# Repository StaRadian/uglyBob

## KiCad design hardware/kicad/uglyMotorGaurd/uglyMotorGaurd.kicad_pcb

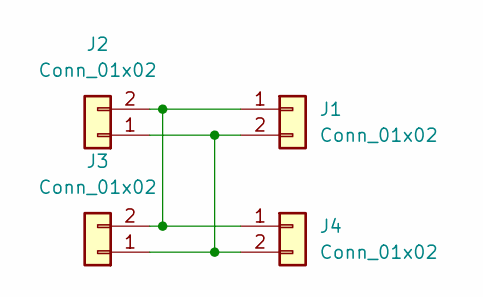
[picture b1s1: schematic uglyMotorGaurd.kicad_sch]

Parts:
J1, J2, J3, J4: Conn_01x02; uglyMotor

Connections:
unnamed: J1.1, J2.2, J3.2, J4.1
unnamed: J1.2, J2.1, J3.1, J4.2

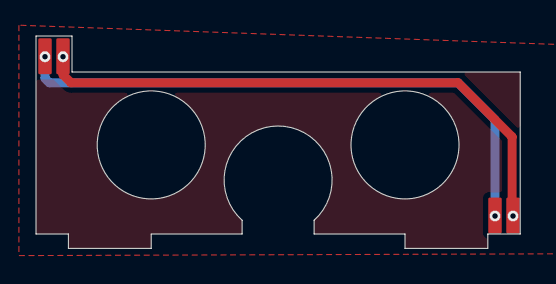
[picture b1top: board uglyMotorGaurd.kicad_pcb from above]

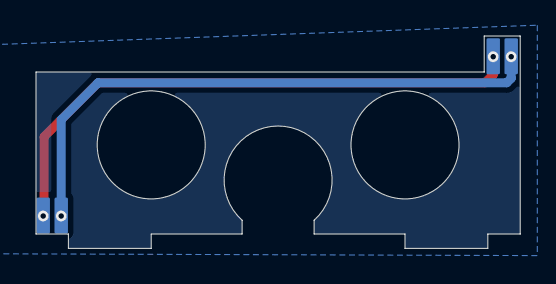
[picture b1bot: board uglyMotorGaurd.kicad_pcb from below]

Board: 2 copper layers, 26.9 x 11.8 mm, 4 parts (2 on the bottom side), 2 nets.

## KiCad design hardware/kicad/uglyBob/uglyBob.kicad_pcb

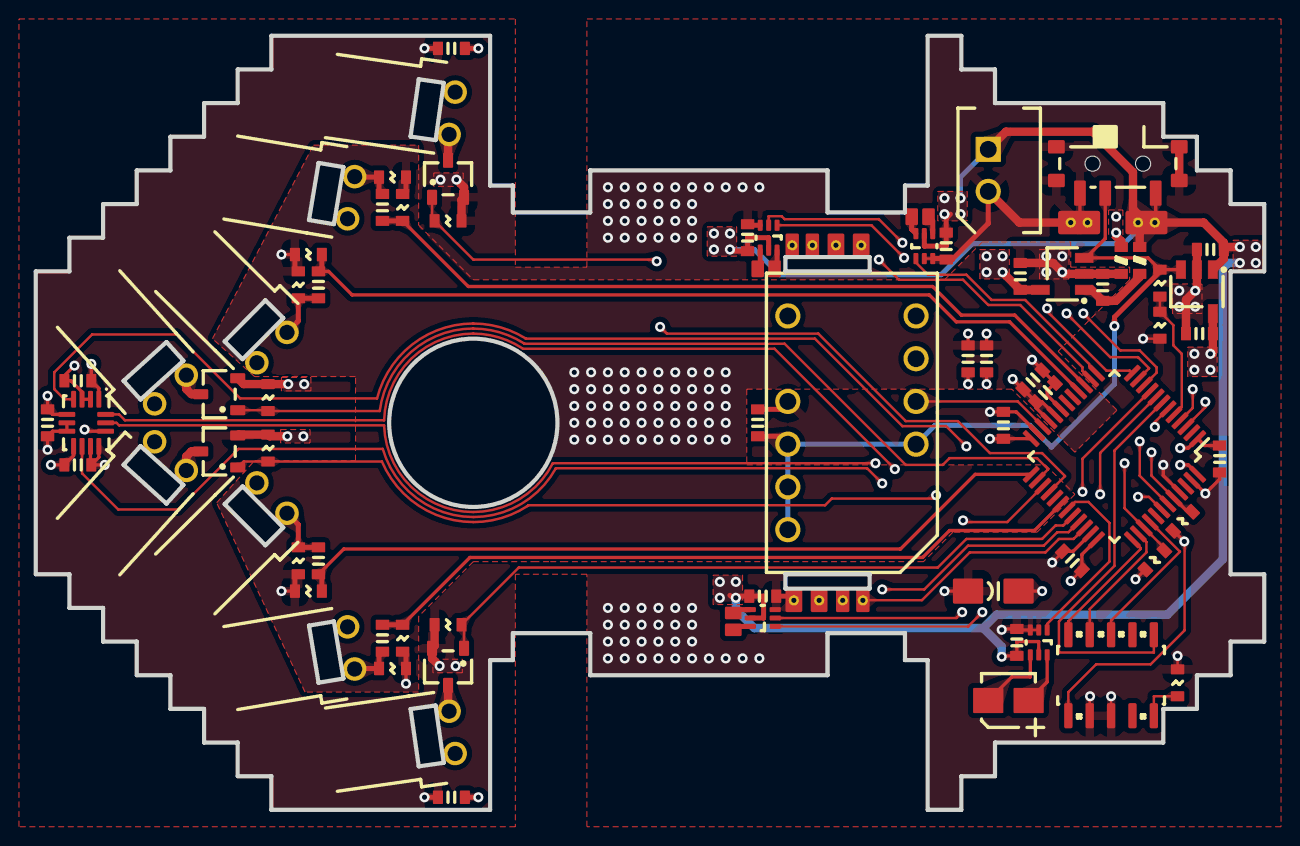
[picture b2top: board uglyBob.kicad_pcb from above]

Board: 4 copper layers, 73.0 x 46.0 mm, 70 parts (0 on the bottom side), 55 nets.

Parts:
BZ1: CMT-322-65-SMT-TR; CMT-332-65-SMT-TR
C1, C2, C3, C4, C5, C6: 1uF; 0603_1608_C
C7, C10, C11, C12, C22, C24, C25, C26, C27, C28: 100nF; 0603_1608_C
C8, C21: 10nF; 0603_1608_C
C9: 4.7uF; 1206_3216_C_Polarized_HandSolder
C13, C14, C15, C16: 2nF; 0603_1608_C
C17, C20, C23: 2.2uF; 0603_1608_C
D1: SFH4550; BobIRLED
FB1, FB2: 600R@100MHz; 0603_1608_L
J1: Battery_Conn; batteryConnector
J2: Charge_Conn; 5267-02A
J3: Conn_02x05_Odd_Even; FTSH-105-01-L-DV-K
J4: Right_Encoder_Conn; AS5047Connector
J5: Left_Encoder_Conn; AS5047Connector
J6: RMotor_Conn; MotorConnector
J7: LMotor_Conn; MotorConnector
J8: SMotor_Conn; MotorConnector
R1: 100; 0603_1608_R
R2, R3, R4, R5, R6, R7, R8, R9: 1.2M; 0603_1608_R
R10, R11, R16, R17: 10k; 0603_1608_R
R12, R13, R14, R15: 30k; 0603_1608_R
SW1: SW_SPDT; EG1215AA
U1, U2: TPS7A2033PDBVR; SOT-23-5_HandSoldering_without4
U3: STM32G4xxC; LQFP-48_7x7mm_P0.5mm
U4: SFH313FA; BobIRSensor
U5, U6, U7, U8: PMV15ENER; SOT-23
U9: ICM-42688-V; LGA-14_2.5x3x0.91_long
U10, U11, U12, U14: DRV8212DRLR; SOT-563
U13: HCMS-390X; HCMS-390x

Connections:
+3.3V: C4.1, C9.1, C10.1, C11.1, C12.1, C17.2, C20.2, C21.2, C22.2, C23.2, D1.FL2 (A), D1.FR2 (A), D1.SL2 (A), D1.SR2 (A), J3.1, J4.3, J5.3, R16.1, R17.1, U2.5 (OUT), U3.1 (VBAT), U3.24 (VDD), U3.36 (VDD), U3.48 (VDD), U9.1 (AP_SDO/AP_AD0), U9.5 (VDDIO), U9.8 (VDD), U9.12 (AP_CS)
+3.3VA: C2.1, C5.1, C6.1, C7.1, C8.1, U1.5 (OUT), U3.20 (VREF+), U3.21 (VDDA), U4.FL1 (C), U4.FR1 (C), U4.SL1 (C), U4.SR1 (C)
+BATT: C3.1, C24.2, C25.2, C26.2, C28.2, FB1.2, J1.1, J2.1, SW1.1 (C), U2.1 (IN), U10.5 (VM), U11.5 (VM), U12.5 (VM), U14.5 (VM)
Batt_voltage: R10.2, R11.1, U3.5 (PF0)
Buzzer_PWM: U3.31 (PA9), U14.1 (IN1)
FL_LED: R12.1, U3.32 (PA10), U5.1 (G1)
FL_SEN: C13.2, R3.1, U3.30 (PA8)
FR_LED: R15.1, U3.28 (PB14), U8.1 (G1)
FR_SEN: C16.2, R9.1, U3.15 (PA7)
GND: C3.2, C4.2, C9.2, C10.2, C11.2, C12.2, C17.1, C20.1, C21.1, C22.1, C23.1, C24.1, C25.1, C26.1, C27.1, C28.1, FB2.1, J1.2, J2.2, J3.3, J3.5, J4.4, J5.4, R1.1, R11.2, R12.2, R13.2, R14.2, R15.2, SW1.3 (A), SW1.EP, U2.2 (GND), U3.23 (VSS), U3.35 (VSS), U3.45 (PB8-BOOT0), U3.47 (VSS), U5.2 (S1), U6.2 (S1), U7.2 (S1), U8.2 (S1), U9.2 (RESV), U9.3 (RESV), U9.6 (GND), U9.7 (RESV), U9.10 (RESV), U9.11 (RESV), U10.3 (GND), U11.3 (GND), U12.2 (IN2), U12.3 (GND), U13.9 (GND), U14.2 (IN2), U14.3 (GND)
GNDA: C1.2, C2.2, C5.2, C6.2, C7.2, C8.2, FB2.2, R2.2, R3.2, R4.2, R5.2, R6.2, R7.2, R8.2, R9.2, U1.2 (GND), U3.19 (VSSA)
HCMS_CE: U3.3 (PC14), U13.7 (CE)
HCMS_CLK: U3.4 (PC15), U13.6 (CLK)
HCMS_DA: U3.22 (PB10), U13.4 (DATA_IN)
HCMS_RS: U3.6 (PF1), U13.5 (RS)
IMU_AP_SCL: R16.2, U3.39 (PA15), U9.13 (AP_SCL/AP_SCLK)
IMU_AP_SDA: R17.2, U3.44 (PB7), U9.14 (AP_SDA/AP_SDIO/AP_SDI)
IMU_CLKIN: U3.42 (PB5), U9.9 (INT2/FSYNC/CLKIN)
IMU_INT: U3.43 (PB6), U9.4 (INT1/INT)
LMotor_IN1: U3.8 (PA0), U11.1 (IN1)
LMotor_IN2: U3.9 (PA1), U11.2 (IN2)
Left_A: J5.1, U3.34 (PA12)
Left_B: J5.2, U3.33 (PA11)
unnamed: BZ1.2 (+), U14.4 (OUT2)
unnamed: BZ1.1 (-), U14.6 (OUT1)
unnamed: D1.FL1 (K), U5.3 (D1)
unnamed: D1.SL1 (K), U6.3 (D1)
unnamed: D1.SR1 (K), U7.3 (D1)
unnamed: D1.FR1 (K), U8.3 (D1)
unnamed: J3.9, R1.2
unnamed: J6.1, U10.6 (OUT1)
unnamed: J6.2, U10.4 (OUT2)
unnamed: J7.1, U11.6 (OUT1)
unnamed: J7.2, U11.4 (OUT2)
unnamed: J8.1, U12.6 (OUT1)
unnamed: J8.2, U12.4 (OUT2)
unnamed: C1.1, FB1.1, U1.1 (IN)
unnamed: C13.1, R2.1, U4.FL2 (E)
unnamed: C14.1, R4.1, U4.SL2 (E)
unnamed: C15.1, R6.1, U4.SR2 (E)
unnamed: C16.1, R8.1, U4.FR2 (E)
Power_EN: C27.2, R10.1, SW1.2 (B), U1.3 (EN), U2.3 (EN), U13.3 (V_LED), U13.10 (SEL), U13.11 (V_LOGIC), U13.12 (RESET)
RMotor_IN1: U3.11 (PA3), U10.1 (IN1)
RMotor_IN2: U3.10 (PA2), U10.2 (IN2)
Right_A: J4.1, U3.14 (PA6)
Right_B: J4.2, U3.12 (PA4)
SL_LED: R13.1, U3.27 (PB13), U6.1 (G1)
SL_SEN: C14.2, R5.1, U3.25 (PB11)
SMotor_PWM: U3.13 (PA5), U12.1 (IN1)
SR_LED: R14.1, U3.26 (PB12), U7.1 (G1)
SR_SEN: C15.2, R7.1, U3.16 (PB0)
SWCLK: J3.4, U3.38 (PA14)
SWDIO: J3.2, U3.37 (PA13)
SWO: J3.6, U3.40 (PB3)
mcu_reset: J3.10, U3.7 (PG10-NRST)

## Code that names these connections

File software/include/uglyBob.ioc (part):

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Mcu.Name=STM32G474C(B-C-E)Tx
Mcu.Package=LQFP48
Mcu.UserName=STM32G474CETx
PA0.Signal=S_TIM5_CH1
PA1.Signal=S_TIM5_CH2
PA10.Mode=Output_TB1
PA10.Signal=HRTIM1_CHB1
PA11.Signal=S_TIM4_CH1
PA12.Signal=S_TIM4_CH2
PA13.Mode=Trace_Asynchronous_SW
PA13.Signal=SYS_JTMS-SWDIO
PA14.Mode=Trace_Asynchronous_SW
PA14.Signal=SYS_JTCK-SWCLK
PA15.Mode=I2C
PA15.Signal=I2C1_SCL
PA2.Signal=S_TIM5_CH3
PA3.Signal=S_TIM5_CH4
PA4.Signal=S_TIM3_CH2
PA5.Signal=S_TIM2_CH1
PA6.Signal=S_TIM3_CH1
PA7.Mode=PGA_Internally_Connected
PA7.Signal=OPAMP2_VINP
PA8.Mode=Output_TA1
PA8.Signal=HRTIM1_CHA1
PA9.Signal=S_TIM2_CH3
PB0.Mode=PGA_Internally_Connected
PB0.Signal=OPAMP3_VINP
PB10.GPIOParameters=GPIO_Label
PB10.GPIO_Label=HCMS_DA
PB10.Signal=GPIO_Output
PB11.Mode=PGA_Internally_Connected
PB11.Signal=OPAMP4_VINP
PB12.Mode=Output_TC1
PB12.Signal=HRTIM1_CHC1
PB13.Mode=PGA_Internally_Connected
PB13.Signal=OPAMP6_VINP
PB14.Mode=Output_TD1
PB14.Signal=HRTIM1_CHD1
PB3.Mode=Trace_Asynchronous_SW
PB3.Signal=SYS_JTDO-SWO
PB5.Signal=S_TIM17_CH1
PB7.Mode=I2C
PB7.Signal=I2C1_SDA
PB9.Signal=GPIO_Output
PC14-OSC32_IN.GPIOParameters=GPIO_Label
PC14-OSC32_IN.GPIO_Label=HCMS_CE
PC14-OSC32_IN.Signal=GPIO_Output
PC15-OSC32_OUT.GPIOParameters=GPIO_Label
PC15-OSC32_OUT.GPIO_Label=HCMS_CK
PC15-OSC32_OUT.Signal=GPIO_Output
PF0-OSC_IN.Mode=IN10-Single-Ended
PF0-OSC_IN.Signal=ADC1_IN10
PF1-OSC_OUT.GPIOParameters=GPIO_Label
PF1-OSC_OUT.GPIO_Label=HCMS_RS
PF1-OSC_OUT.Signal=GPIO_Output
RCC.HSE_VALUE=8000000
RCC.SYSCLKFreq_VALUE=170000000
RCC.SYSCLKSource=RCC_SYSCLKSOURCE_PLLCLK
board=custom
